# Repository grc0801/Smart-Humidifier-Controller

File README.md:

# Smart Humidifier Controller using ATmega328P – KiCAD Simulation + Arduino Firmware

This project simulates a Bluetooth-enabled smart humidifier controller using the ATmega328P microcontroller. It features both manual and wireless control using a push button and HC-05 Bluetooth module. The system also includes status LED output and MOSFET switching for humidifier control.

The schematic and PCB layout were designed using KiCAD and verified with 0 DRC errors. Firmware is written in Arduino IDE and ready for upload via ISP after fabrication.

---

## 🔧 Features

- Manual control via push button (PD2)
- Wireless Bluetooth control via HC-05 (UART)
- LED status indication
- MOSFET-based humidifier switching
- KiCAD-verified schematic and PCB layout
- Ready-to-fabricate Gerber and drill files

---

## 🛠 Tools Used

- KiCAD (Schematic + PCB Design)
- Arduino IDE (Embedded Firmware)
- Gerber Generator (Production Output)

---

## 🚀 How to Use

1. Open the schematic and layout in KiCAD.
2. Review firmware code in Arduino IDE.
3. After PCB fabrication, upload code to ATmega328P using USBasp or Arduino UNO as ISP.
4. Power the board via 5V and control the humidifier manually or over Bluetooth.

---

## ✅ Result

- Complete circuit and PCB simulated successfully in KiCAD  
- 0 DRC errors and clean layout with modular headers  
- Functional Arduino firmware tested in simulation  
- Project is ready for fabrication and deployment

---

## 💡 Future Scope

- Add automatic humidity sensing and closed-loop control
- Optimize PCB layout using SMD components
- Add OLED/LCD for system feedback
- Integrate voltage regulation and protection

---

## 🙌 Created By

**GIRIDHARAN B**
*if you find any mistake or improvement to be done, let me know*
---

**License**: MIT (for educational use)

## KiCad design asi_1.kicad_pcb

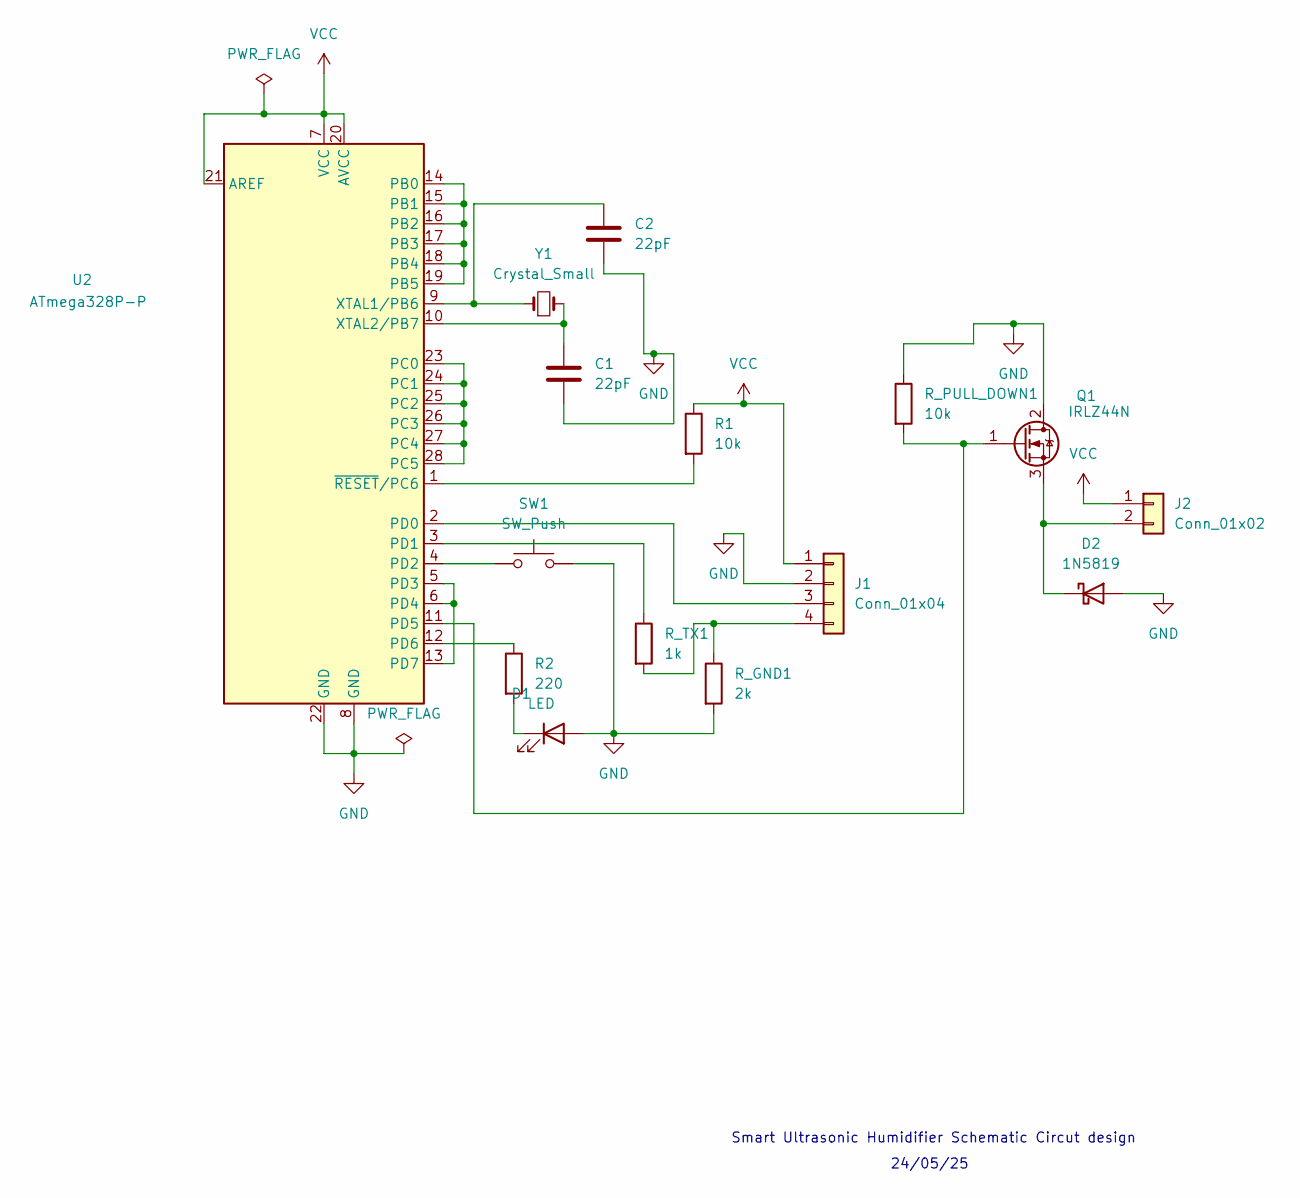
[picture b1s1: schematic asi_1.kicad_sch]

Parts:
C1, C2: 22pF; C_Disc_D5.0mm_W2.5mm_P5.00mm
D1: LED; LED_D5.0mm
D2: 1N5819; D_DO-41_SOD81_P10.16mm_Horizontal
J1: Conn_01x04; PinHeader_1x04_P2.54mm_Vertical
J2: Conn_01x02; PinHeader_1x02_P2.54mm_Vertical
Q1: IRLZ44N; TO-220-3_Vertical
R1: 10k; R_Axial_DIN0207_L6.3mm_D2.5mm_P7.62mm_Horizontal
R2: 220; R_Axial_DIN0207_L6.3mm_D2.5mm_P7.62mm_Horizontal
R_GND1: 2k; R_Axial_DIN0207_L6.3mm_D2.5mm_P7.62mm_Horizontal
R_PULL_DOWN1: 10k; R_Axial_DIN0207_L6.3mm_D2.5mm_P7.62mm_Horizontal
R_TX1: 1k; R_Axial_DIN0207_L6.3mm_D2.5mm_P7.62mm_Horizontal
SW1: SW_Push; TO-220-3_Vertical
U2: ATmega328P-P; DIP-28_W7.62mm
Y1: Crystal_Small; Crystal_HC49-U_Vertical

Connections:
GND: C1.2, C2.2, D1.2 (A), D2.2 (A), J1.2, Q1.2 (D), R_GND1.2, R_PULL_DOWN1.1, SW1.2, U2.8 (GND), U2.22 (GND)
unnamed: D1.1 (K), R2.2
unnamed: D2.1 (K), J2.2, Q1.3 (S)
unnamed: J1.3, U2.2 (PD0)
unnamed: J1.4, R_GND1.1, R_TX1.2
unnamed: Q1.1 (G), R_PULL_DOWN1.2, U2.11 (PD5)
unnamed: U2.14 (PB0), U2.15 (PB1), U2.16 (PB2), U2.17 (PB3), U2.18 (PB4), U2.19 (PB5)
unnamed: U2.23 (PC0), U2.24 (PC1), U2.25 (PC2), U2.26 (PC3), U2.27 (PC4), U2.28 (PC5)
unnamed: R_TX1.1, U2.3 (PD1)
unnamed: SW1.1, U2.4 (PD2)
unnamed: U2.5 (PD3), U2.6 (PD4), U2.13 (PD7)
unnamed: R2.1, U2.12 (PD6)
unnamed: C2.1, U2.9 (XTAL1/PB6), Y1.1
unnamed: C1.1, U2.10 (XTAL2/PB7), Y1.2
unnamed: R1.2, U2.1 (~RESET/PC6)
VCC: J1.1, J2.1, R1.1, U2.7 (VCC), U2.20 (AVCC), U2.21 (AREF)

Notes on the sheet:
Smart Ultrasonic Humidifier Schematic Circut design
24/05/25

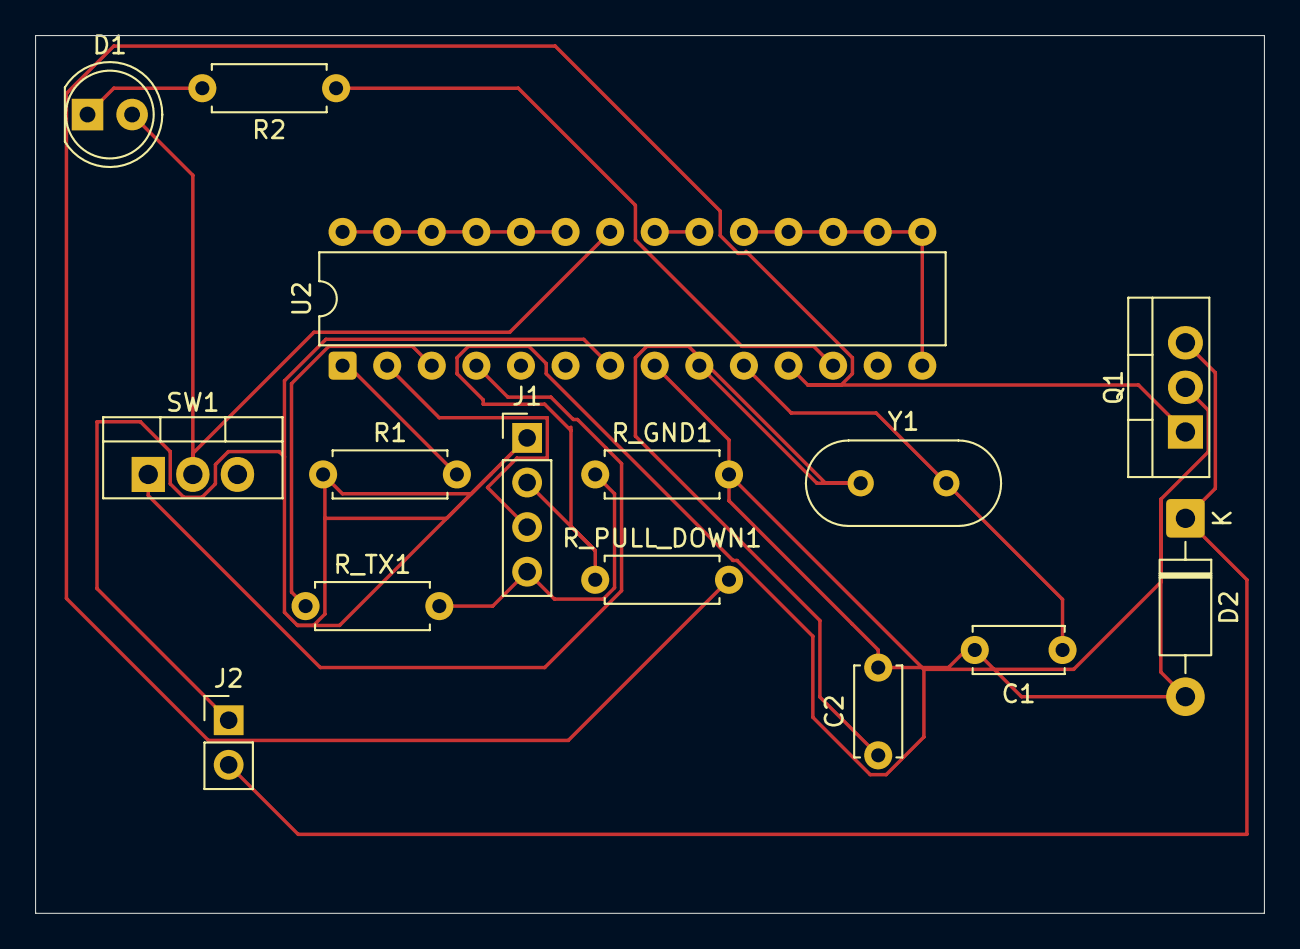
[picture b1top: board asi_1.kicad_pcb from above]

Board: 2 copper layers, 70.0 x 50.0 mm, 15 parts (0 on the bottom side), 16 nets.

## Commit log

2025-06-18 README.md
